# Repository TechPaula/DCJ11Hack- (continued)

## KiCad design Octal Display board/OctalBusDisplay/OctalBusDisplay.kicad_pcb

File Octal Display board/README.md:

# Octal Bus Display
This sadly never worked, and it also pulled a LOT of current (>2A), so I've abandoned it.
D

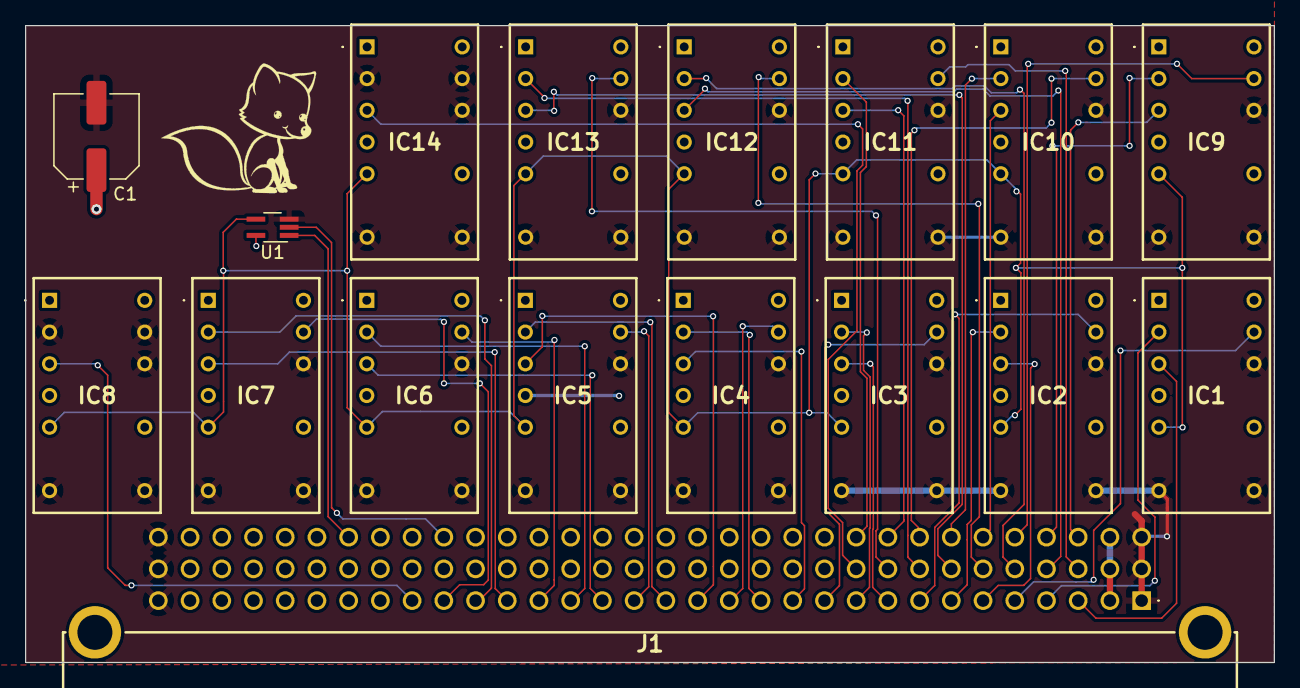
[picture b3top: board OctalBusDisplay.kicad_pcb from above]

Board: 2 copper layers, 100.0 x 51.0 mm, 18 parts (0 on the bottom side), 43 nets.

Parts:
C1: 47uF 16V; CP_Elec_6.3x5.8
IC1, IC2, IC3, IC4, IC5, IC6, IC7, IC8, IC9, IC10, IC11, IC12, IC13, IC14: TIL311
J1: 86093967113745ELF
SYM1: Logo_Open_Hardware_Large; Fox_avatar_18mm
U1: 74AHC1G08; SOT-353_SC-70-5_Handsoldering

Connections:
/DA0: IC9.3 (DATA_A), J1.C3
/DA1: IC9.2 (DATA_B), J1.C4
/DA2: IC9.13 (DATA_C), J1.C5
/DA3: IC10.3 (DATA_A), J1.C6
/DA4: IC10.2 (DATA_B), J1.C7
/DA5: IC10.13 (DATA_C), J1.C8
/DA6: IC11.3 (DATA_A), J1.C9
/DA7: IC11.2 (DATA_B), J1.C10
/DA8: IC11.13 (DATA_C), J1.B3
/DA9: IC12.3 (DATA_A), J1.B4
/DA10: IC12.2 (DATA_B), J1.B5
/DA11: IC12.13 (DATA_C), J1.B6
/DA12: IC13.3 (DATA_A), J1.B7
/DA13: IC13.2 (DATA_B), J1.B8
/DA14: IC13.13 (DATA_C), J1.B9
/DA15: IC14.3 (DATA_A), J1.B10
/LA0: IC1.3 (DATA_A), J1.A3
/LA1: IC1.2 (DATA_B), J1.A4
/LA2: IC1.13 (DATA_C), J1.A5
/LA3: IC2.3 (DATA_A), J1.A6
/LA4: IC2.2 (DATA_B), J1.A7
/LA5: IC2.13 (DATA_C), J1.A8
/LA6: IC3.3 (DATA_A), J1.A9
/LA7: IC3.2 (DATA_B), J1.A10
/LA8: IC3.13 (DATA_C), J1.A11
/LA9: IC4.3 (DATA_A), J1.A12
/LA10: IC4.2 (DATA_B), J1.A13
/LA11: IC4.13 (DATA_C), J1.A14
/LA12: IC5.3 (DATA_A), J1.A15
/LA13: IC5.2 (DATA_B), J1.A16
/LA14: IC5.13 (DATA_C), J1.A17
/LA15: IC6.3 (DATA_A), J1.A18
/LA16: IC6.2 (DATA_B), J1.A19
/LA17: IC6.13 (DATA_C), J1.A20
/LA18: IC7.3 (DATA_A), J1.A21
/LA19: IC7.2 (DATA_B), J1.A22
/LA20: IC7.13 (DATA_C), J1.A23
/LA21: IC8.3 (DATA_A), J1.A24
GND: C1.2, IC1.7 (GND), IC1.8 (BLANK), IC1.12 (DATA_D), IC2.7 (GND), IC2.8 (BLANK), IC2.12 (DATA_D), IC3.7 (GND), IC3.8 (BLANK), IC3.12 (DATA_D), IC4.7 (GND), IC4.8 (BLANK), IC4.12 (DATA_D), IC5.7 (GND), IC5.8 (BLANK), IC5.12 (DATA_D), IC6.7 (GND), IC6.8 (BLANK), IC6.12 (DATA_D), IC7.7 (GND), IC7.8 (BLANK), IC7.12 (DATA_D), IC8.2 (DATA_B), IC8.7 (GND), IC8.8 (BLANK), IC8.12 (DATA_D), IC8.13 (DATA_C), IC9.7 (GND), IC9.8 (BLANK), IC9.12 (DATA_D), IC10.7 (GND), IC10.8 (BLANK), IC10.12 (DATA_D), IC11.7 (GND), IC11.8 (BLANK), IC11.12 (DATA_D), IC12.7 (GND), IC12.8 (BLANK), IC12.12 (DATA_D), IC13.7 (GND), IC13.8 (BLANK), IC13.12 (DATA_D), IC14.2 (DATA_B), IC14.7 (GND), IC14.8 (BLANK), IC14.12 (DATA_D), IC14.13 (DATA_C), J1.A1, J1.A32, J1.B1, J1.B32, J1.C1, J1.C32, U1.3 (GND)
unnamed: IC1.5 (STROBE), IC2.5 (STROBE), IC3.5 (STROBE), IC4.5 (STROBE), IC5.5 (STROBE), IC6.5 (STROBE), IC7.5 (STROBE), IC8.5 (STROBE), IC9.5 (STROBE), IC10.5 (STROBE), IC11.5 (STROBE), IC12.5 (STROBE), IC13.5 (STROBE), IC14.5 (STROBE), U1.4
RAM_nWE: J1.C23, U1.2
VCC: C1.1, IC1.1 (LED_V), IC1.14 (VIN), IC2.1 (LED_V), IC2.14 (VIN), IC3.1 (LED_V), IC3.14 (VIN), IC4.1 (LED_V), IC4.14 (VIN), IC5.1 (LED_V), IC5.14 (VIN), IC6.1 (LED_V), IC6.14 (VIN), IC7.1 (LED_V), IC7.14 (VIN), IC8.1 (LED_V), IC8.14 (VIN), IC9.1 (LED_V), IC9.14 (VIN), IC10.1 (LED_V), IC10.14 (VIN), IC11.1 (LED_V), IC11.14 (VIN), IC12.1 (LED_V), IC12.14 (VIN), IC13.1 (LED_V), IC13.14 (VIN), IC14.1 (LED_V), IC14.14 (VIN), J1.A2, J1.B2, J1.C2, U1.5 (VCC)
nBUFCTL: J1.C26, U1.1

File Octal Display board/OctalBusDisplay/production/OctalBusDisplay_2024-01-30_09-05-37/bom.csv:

Designator,Footprint,Quantity,Value,LCSC Part #
C1,CP_Elec_6.3x5.8,1,47uF 16V,
"IC1, IC10, IC11, IC12, IC13, IC14, IC2, IC3, IC4, IC5, IC6, IC7, IC8, IC9",TIL311,14,TIL311,
J1,86093967113745ELF,1,86093967113745ELF,
U1,SOT-353_SC-70-5_Handsoldering,1,74AHC1G08,

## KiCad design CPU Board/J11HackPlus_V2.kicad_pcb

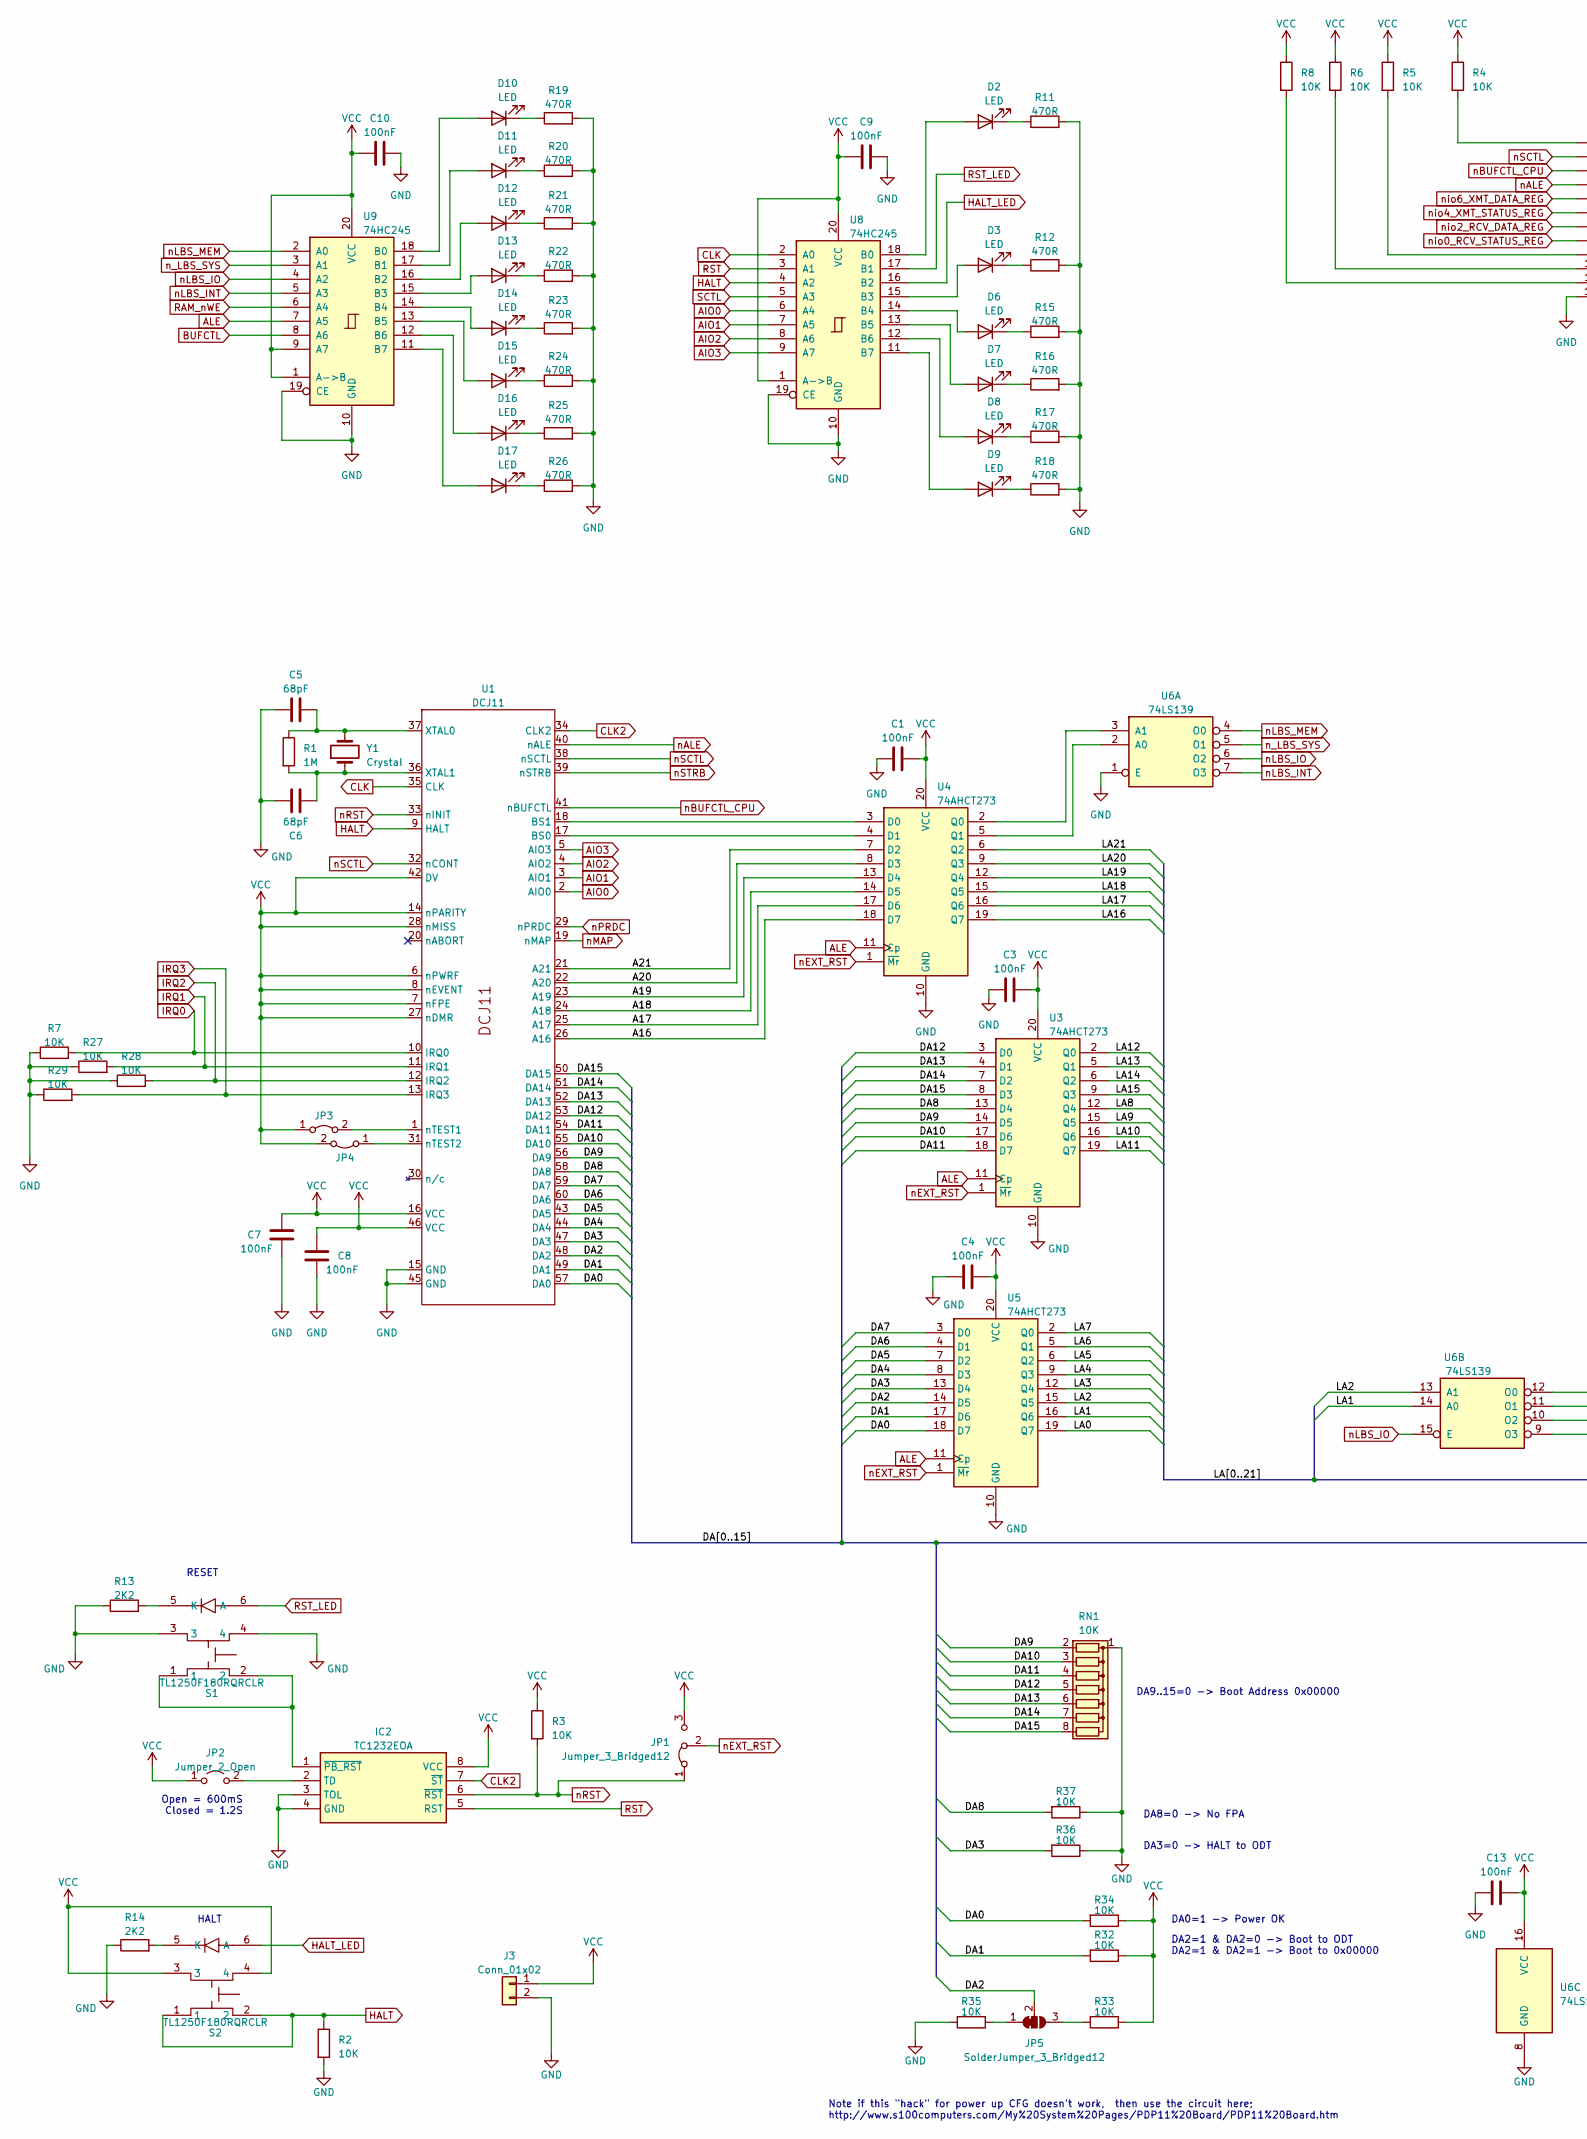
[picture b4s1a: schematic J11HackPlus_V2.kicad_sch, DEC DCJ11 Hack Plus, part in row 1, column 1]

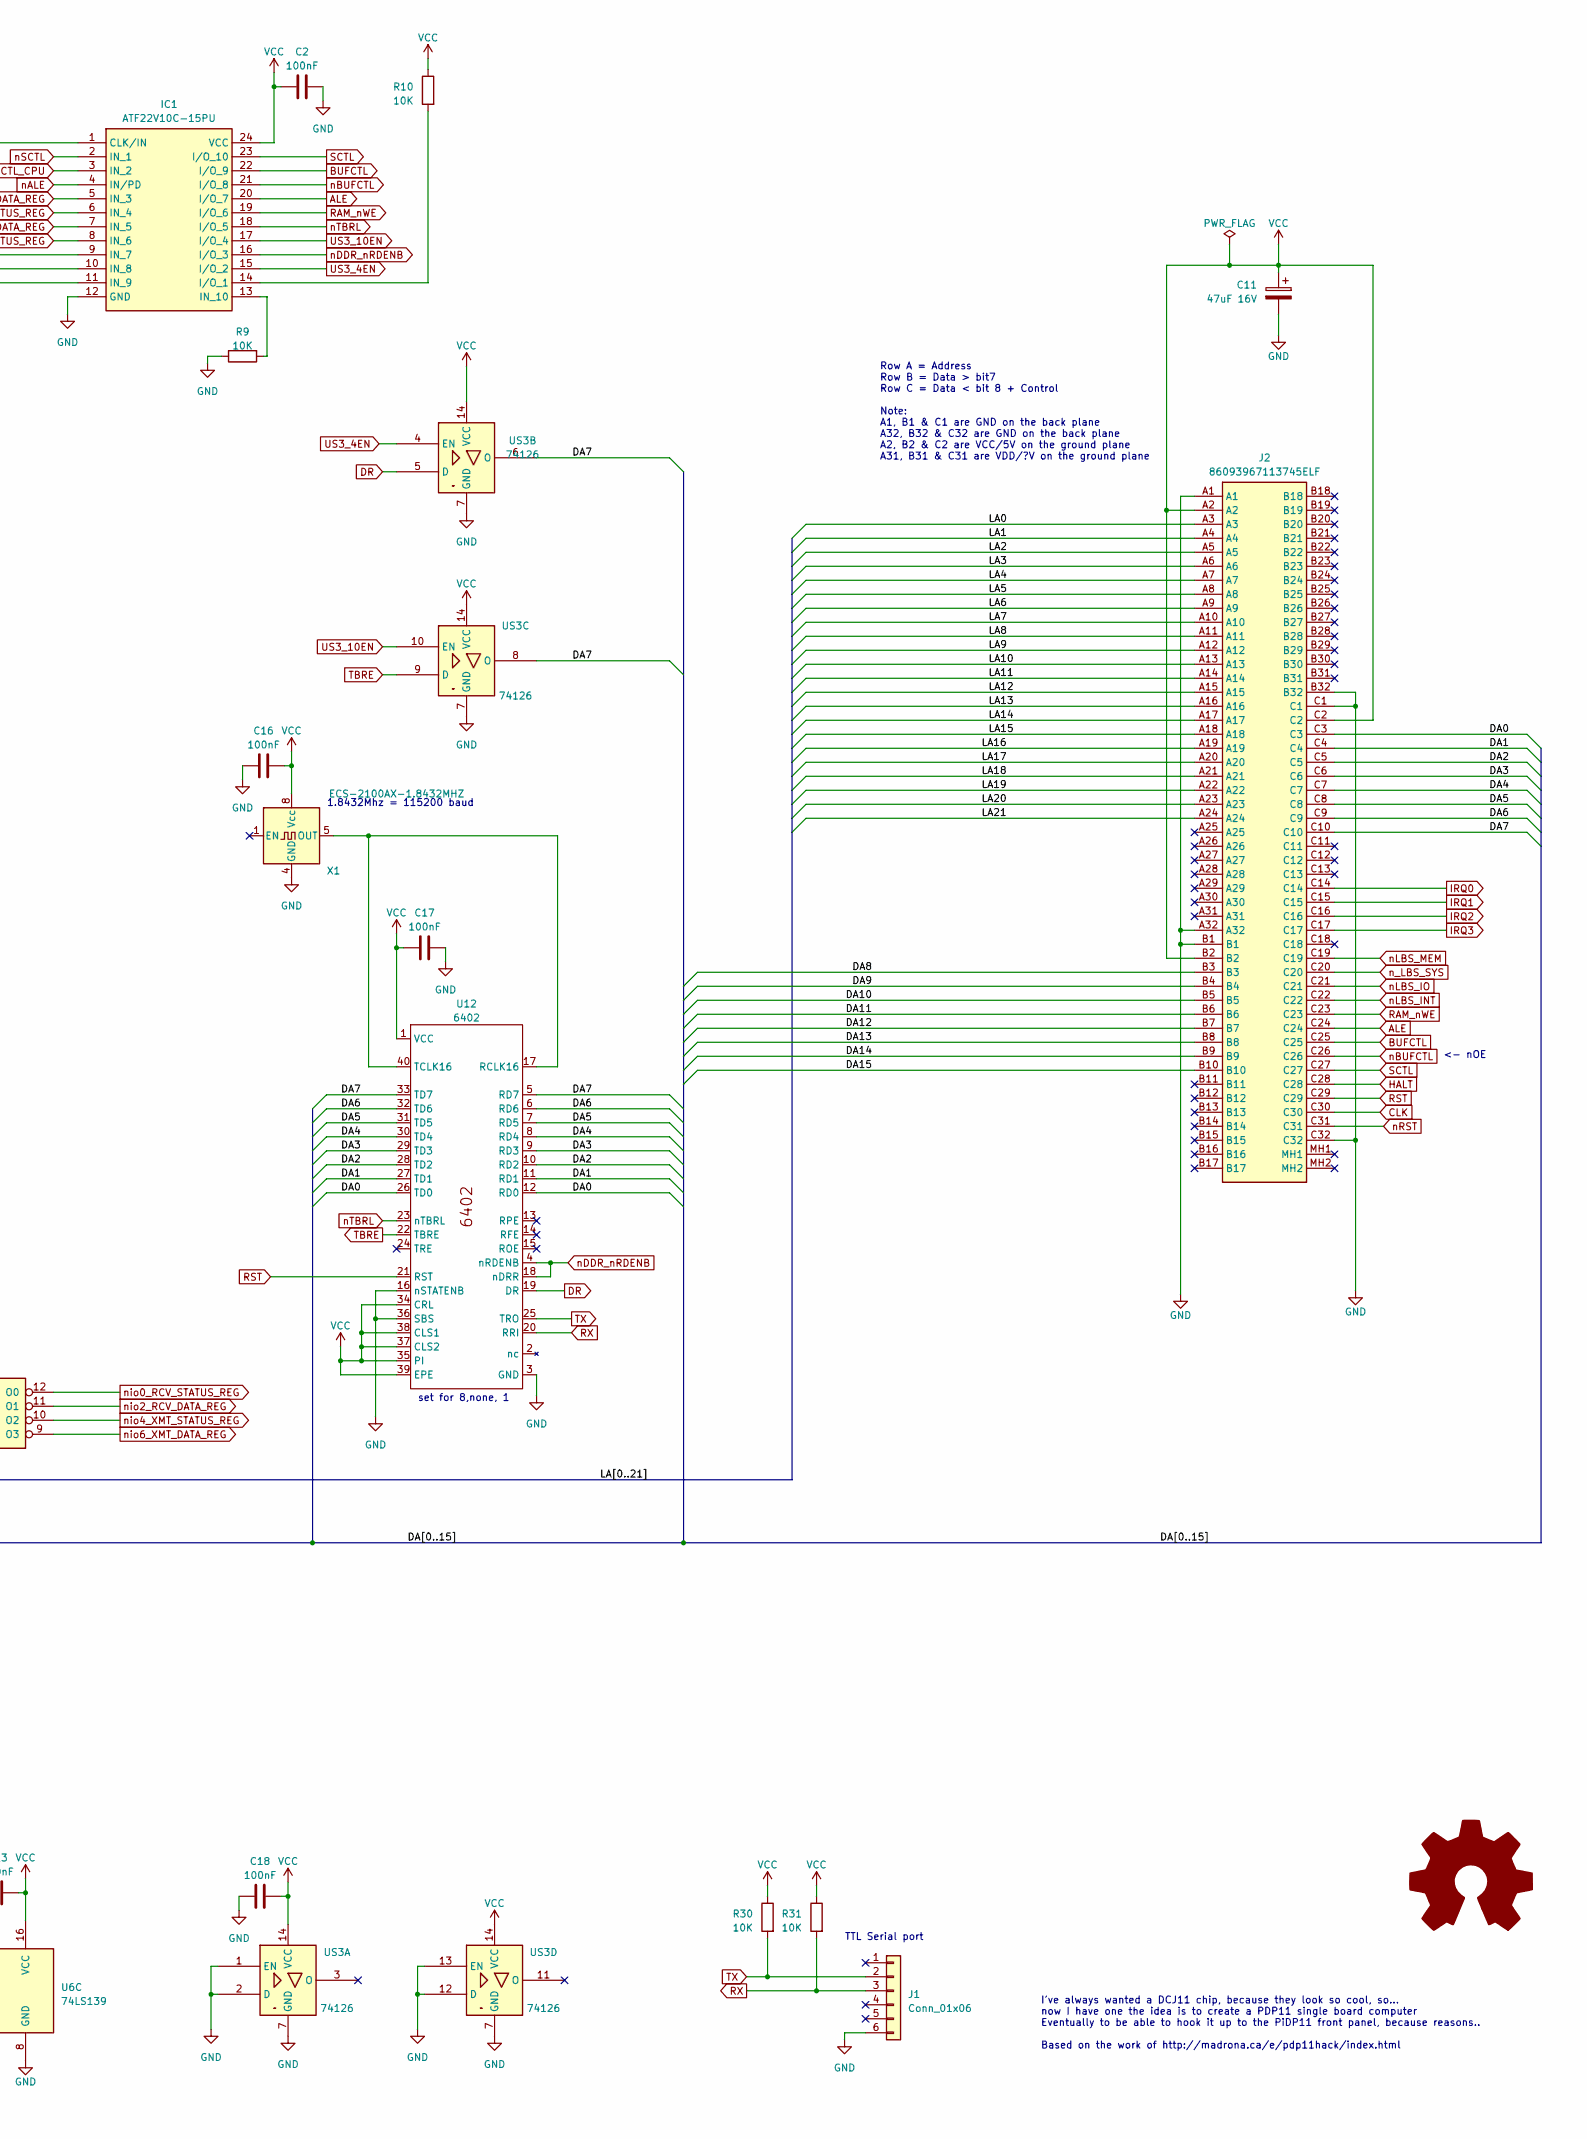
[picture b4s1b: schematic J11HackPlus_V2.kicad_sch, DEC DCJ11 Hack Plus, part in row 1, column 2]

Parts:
C1, C2, C3, C4, C7, C8, C9, C10, C13, C16, C17, C18: 100nF; C_0603_1608Metric_Pad1.08x0.95mm_HandSolder
C5, C6: 68pF; C_0603_1608Metric_Pad1.08x0.95mm_HandSolder
C11: 47uF 16V; CP_Elec_6.3x5.8
D2, D3, D6, D7, D8, D9, D10, D11, D12, D13, D14, D15, D16, D17: LED; LTL4221NHBP
IC1: ATF22V10C-15PU; DIP-24_W7.62mm; Manufacturer_Part_Number ATF22V10C-15PU; Mouser Part Number 556-AF22V10C15PU
IC2: TC1232EOA; SOIC-8_3.9x4.9mm_P1.27mm; Manufacturer_Part_Number TC1232EOA; Mouser Part Number 579-TC1232EOA
J1: Conn_01x06; PinHeader_1x06_P2.54mm_Vertical
J2: 86093967113745ELF; Manufacturer_Part_Number 86093967113745ELF
J3: Conn_01x02; Molex_KK-396_5273-02A_1x02_P3.96mm_Vertical
JP1: Jumper_3_Bridged12; SolderJumper-3_P1.3mm_Bridged2Bar12_RoundedPad1.0x1.5mm_Num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
JP2: Jumper_2_Open; SolderJumper-2_P1.3mm_Open_RoundedPad1.0x1.5mm
JP3, JP4: Jumper_2_Bridged; SolderJumper-2_P1.3mm_Bridged2Bar_RoundedPad1.0x1.5mm
JP5: SolderJumper_3_Bridged12; SolderJumper-3_P1.3mm_Bridged12_RoundedPad1.0x1.5mm_NumberL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
R1: 1M; R_0603_1608Metric_Pad0.98x0.95mm_HandSolder
R2, R3, R4, R5, R6, R7, R8, R9, R10, R27, R28, R29, R30, R31, R32, R33, R34, R35, R36, R37: 10K; R_0603_1608Metric_Pad0.98x0.95mm_HandSolder
R11, R12, R15, R16, R17, R18, R19, R20, R21, R22, R23, R24, R25, R26: 470R; R_0603_1608Metric_Pad0.98x0.95mm_HandSolder
R13, R14: 2K2; R_0603_1608Metric_Pad0.98x0.95mm_HandSolder
RN1: 10K; R_Array_SIP8
S1, S2: TL1250F180RQRCLR; Mouser Part Number 612-TL1250F180RQRCLR
SYM1: Logo_Open_Hardware_Large; Fox_avatar_18mm
U1: DCJ11; DIP-60_1300_ELL
U3, U4, U5: 74AHCT273; SSOP-20_5.3x7.2mm_P0.65mm
U6: 74LS139; SSOP-16_4.4x5.2mm_P0.65mm
U8, U9: 74HC245; TSSOP-20_4.4x6.5mm_P0.65mm
U12: 6402; DIP-40_W15.24mm_Socket
US3: 74126; SOIC-14_3.9x8.7mm_P1.27mm
X1: ECS-2100AX-1.8432MHZ; Oscillator_DIP-8
Y1: Crystal; Crystal_HC18-U_Vertical

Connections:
/A16: U1.26 (A16), U4.18 (D7)
/A17: U1.25 (A17), U4.17 (D6)
/A18: U1.24 (A18), U4.14 (D5)
/A19: U1.23 (A19), U4.13 (D4)
/A20: U1.22 (A20), U4.8 (D3)
/A21: U1.21 (A21), U4.7 (D2)
/DA0: J2.C3, R34.2, U1.57 (DA0), U5.18 (D7), U12.12 (RD0), U12.26 (TD0)
/DA1: J2.C4, R32.2, U1.49 (DA1), U5.17 (D6), U12.11 (RD1), U12.27 (TD1)
/DA2: J2.C5, JP5.2 (C), U1.48 (DA2), U5.14 (D5), U12.10 (RD2), U12.28 (TD2)
/DA3: J2.C6, R36.2, U1.47 (DA3), U5.13 (D4), U12.9 (RD3), U12.29 (TD3)
/DA4: J2.C7, U1.44 (DA4), U5.8 (D3), U12.8 (RD4), U12.30 (TD4)
/DA5: J2.C8, U1.43 (DA5), U5.7 (D2), U12.7 (RD5), U12.31 (TD5)
/DA6: J2.C9, U1.60 (DA6), U5.4 (D1), U12.6 (RD6), U12.32 (TD6)
/DA7: J2.C10, U1.59 (DA7), U5.3 (D0), U12.5 (RD7), U12.33 (TD7), US3.6 (O), US3.8 (O)
/DA8: J2.B3, R37.2, U1.58 (DA8), U3.13 (D4)
/DA9: J2.B4, RN1.2 (R1), U1.56 (DA9), U3.14 (D5)
/DA10: J2.B5, RN1.3 (R2), U1.55 (DA10), U3.17 (D6)
/DA11: J2.B6, RN1.4 (R3), U1.54 (DA11), U3.18 (D7)
/DA12: J2.B7, RN1.5 (R4), U1.53 (DA12), U3.3 (D0)
/DA13: J2.B8, RN1.6 (R5), U1.52 (DA13), U3.4 (D1)
/DA14: J2.B9, RN1.7 (R6), U1.51 (DA14), U3.7 (D2)
/DA15: J2.B10, RN1.8 (R7), U1.50 (DA15), U3.8 (D3)
/LA0: J2.A3, U5.19 (Q7)
/LA1: J2.A4, U5.16 (Q6), U6.14 (A0)
/LA2: J2.A5, U5.15 (Q5), U6.13 (A1)
/LA3: J2.A6, U5.12 (Q4)
/LA4: J2.A7, U5.9 (Q3)
/LA5: J2.A8, U5.6 (Q2)
/LA6: J2.A9, U5.5 (Q1)
/LA7: J2.A10, U5.2 (Q0)
/LA8: J2.A11, U3.12 (Q4)
/LA9: J2.A12, U3.15 (Q5)
/LA10: J2.A13, U3.16 (Q6)
/LA11: J2.A14, U3.19 (Q7)
/LA12: J2.A15, U3.2 (Q0)
/LA13: J2.A16, U3.5 (Q1)
/LA14: J2.A17, U3.6 (Q2)
/LA15: J2.A18, U3.9 (Q3)
/LA16: J2.A19, U4.19 (Q7)
/LA17: J2.A20, U4.16 (Q6)
/LA18: J2.A21, U4.15 (Q5)
/LA19: J2.A22, U4.12 (Q4)
/LA20: J2.A23, U4.9 (Q3)
/LA21: J2.A24, U4.6 (Q2)
AIO0: U1.2 (AIO0), U8.6 (A4)
AIO1: U1.3 (AIO1), U8.7 (A5)
AIO2: U1.4 (AIO2), U8.8 (A6)
AIO3: U1.5 (AIO3), U8.9 (A7)
ALE: IC1.20 (I/O_7), J2.C24, U3.11 (Cp), U4.11 (Cp), U5.11 (Cp), U9.7 (A5)
BUFCTL: IC1.22 (I/O_9), J2.C25, U9.8 (A6)
CLK: J2.C30, U1.35 (CLK), U8.2 (A0)
CLK2: IC2.7 (~ST), U1.34 (CLK2)
DR: U12.19 (DR), US3.5 (D)
GND: C1.1, C2.1, C3.1, C4.1, C5.1, C6.2, C7.1, C8.1, C9.1, C10.1, C11.2, C13.1, C16.1, C17.1, C18.1, IC1.12 (GND), IC2.3 (TOL), IC2.4 (GND), J1.6, J2.A1, J2.A32, J2.B1, J2.B32, J2.C1, J2.C32, J3.2, R2.2, R7.1, R9.1, R11.2, R12.2, R13.1, R14.1, R15.2, R16.2, R17.2, R18.2, R19.2, R20.2, R21.2, R22.2, R23.2, R24.2, R25.2, R26.2, R27.1, R28.1, R29.1, R35.2, R36.1, R37.1, RN1.1 (common), S1.3, S1.4, U1.15 (GND), U1.45 (GND), U3.10 (GND), U4.10 (GND), U5.10 (GND), U6.1 (E), U6.8 (GND), U8.10 (GND), U8.19 (CE), U9.10 (GND), U9.19 (CE), U12.3 (GND), U12.16 (nSTATENB), U12.36 (SBS), US3.1 (EN), US3.2 (D), US3.7 (GND), US3.12 (D), US3.13 (EN), X1.4 (GND)
HALT: J2.C28, R2.1, S2.1, S2.2, U1.9 (HALT), U8.4 (A2)
HALT_LED: S2.6 (A), U8.16 (B2)
IRQ0: J2.C14, R7.2, U1.10 (IRQ0)
IRQ1: J2.C15, R27.2, U1.11 (IRQ1)
IRQ2: J2.C16, R28.2, U1.12 (IRQ2)
IRQ3: J2.C17, R29.2, U1.13 (IRQ3)
unnamed: D2.2 (A), U8.18 (B0)
unnamed: D2.1 (K), R11.1
unnamed: D3.2 (A), U8.15 (B3)
unnamed: D3.1 (K), R12.1
unnamed: D6.2 (A), U8.14 (B4)
unnamed: D6.1 (K), R15.1
unnamed: D7.2 (A), U8.13 (B5)
unnamed: D7.1 (K), R16.1
unnamed: D8.2 (A), U8.12 (B6)
unnamed: D8.1 (K), R17.1
unnamed: D9.2 (A), U8.11 (B7)
unnamed: D9.1 (K), R18.1
unnamed: D10.2 (A), U9.18 (B0)
unnamed: D10.1 (K), R19.1
unnamed: D11.2 (A), U9.17 (B1)
unnamed: D11.1 (K), R20.1
unnamed: D12.2 (A), U9.16 (B2)
unnamed: D12.1 (K), R21.1
unnamed: D13.2 (A), U9.15 (B3)
unnamed: D13.1 (K), R22.1
unnamed: D14.2 (A), U9.14 (B4)
unnamed: D14.1 (K), R23.1
unnamed: D15.2 (A), U9.13 (B5)
unnamed: D15.1 (K), R24.1
unnamed: D16.2 (A), U9.12 (B6)
unnamed: D16.1 (K), R25.1
unnamed: D17.2 (A), U9.11 (B7)
unnamed: D17.1 (K), R26.1
unnamed: IC1.1 (CLK/IN), R4.2
unnamed: IC1.9 (IN_7), R5.2
unnamed: IC1.10 (IN_8), R6.2
unnamed: IC1.11 (IN_9), R8.2
unnamed: IC1.13 (IN_10), R9.2
unnamed: IC1.14 (I/O_1), R10.2
unnamed: IC2.2 (TD), JP2.2 (B)
unnamed: IC2.1 (~PB_RST), S1.1, S1.2
unnamed: JP3.2 (B), U1.1 (nTEST1)
unnamed: JP4.1 (A), U1.31 (nTEST2)
unnamed: JP5.1 (A), R35.1
unnamed: JP5.3 (B), R33.2
unnamed: R13.2, S1.5 (K)
unnamed: R14.2, S2.5 (K)
unnamed: U1.17 (BS0), U4.4 (D1)
unnamed: U1.18 (BS1), U4.3 (D0)
unnamed: C5.2, R1.1, U1.37 (XTAL0), Y1.2
unnamed: C6.1, R1.2, U1.36 (XTAL1), Y1.1
unnamed: U4.2 (Q0), U6.3 (A1)
unnamed: U4.5 (Q1), U6.2 (A0)
unnamed: U12.17 (RCLK16), U12.40 (TCLK16), X1.5 (OUT)
RAM_nWE: IC1.19 (I/O_6), J2.C23, U9.6 (A4)
RST: IC2.5 (RST), J2.C29, U8.3 (A1), U12.21 (RST)
RST_LED: S1.6 (A), U8.17 (B1)
RX: J1.3, R31.2, U12.20 (RRI)
SCTL: IC1.23 (I/O_10), J2.C27, U8.5 (A3)
TBRE: U12.22 (TBRE), US3.9 (D)
TX: J1.2, R30.2, U12.25 (TRO)
US3_4EN: IC1.15 (I/O_2), US3.4 (EN)
US3_10EN: IC1.17 (I/O_4), US3.10 (EN)
VCC: C1.2, C2.2, C3.2, C4.2, C7.2, C8.2, C9.2, C10.2, C11.1, C13.2, C16.2, C17.2, C18.2, IC1.24 (VCC), IC2.8 (VCC), J2.A2, J2.B2, J2.C2, J3.1, JP1.3 (B), JP2.1 (A), JP3.1 (A), JP4.2 (B), R3.1, R4.1, R5.1, R6.1, R8.1, R10.1, R30.1, R31.1, R32.1, R33.1, R34.1, S2.3, S2.4, U1.6 (nPWRF), U1.7 (nFPE), U1.8 (nEVENT), U1.14 (nPARITY), U1.16 (VCC), U1.27 (nDMR), U1.28 (nMISS), U1.42 (DV), U1.46 (VCC), U3.20 (VCC), U4.20 (VCC), U5.20 (VCC), U6.16 (VCC), U8.1 (A->B), U8.20 (VCC), U9.1 (A->B), U9.9 (A7), U9.20 (VCC), U12.1 (VCC), U12.34 (CRL), U12.35 (PI), U12.37 (CLS2), U12.38 (CLS1), U12.39 (EPE), US3.14 (VCC), X1.8 (Vcc)
nALE: IC1.4 (IN/PD), U1.40 (nALE)
nBUFCTL: IC1.21 (I/O_8), J2.C26
nBUFCTL_CPU: IC1.3 (IN_2), U1.41 (nBUFCTL)
nDDR_nRDENB: IC1.16 (I/O_3), U12.4 (nRDENB), U12.18 (nDRR)
nEXT_RST: JP1.2 (C), U3.1 (~Mr), U4.1 (~Mr), U5.1 (~Mr)
nLBS_INT: J2.C22, U6.7 (O3), U9.5 (A3)
nLBS_IO: J2.C21, U6.6 (O2), U6.15 (E), U9.4 (A2)
nLBS_MEM: J2.C19, U6.4 (O0), U9.2 (A0)
nMAP: U1.19 (nMAP)
nPRDC: U1.29 (nPRDC)
nRST: IC2.6 (~RST), J2.C31, JP1.1 (A), R3.2, U1.33 (nINIT)
nSCTL: IC1.2 (IN_1), U1.32 (nCONT), U1.38 (nSCTL)
nSTRB: U1.39 (nSTRB)
nTBRL: IC1.18 (I/O_5), U12.23 (nTBRL)
n_LBS_SYS: J2.C20, U6.5 (O1), U9.3 (A1)
nio0_RCV_STATUS_REG: IC1.8 (IN_6), U6.12 (O0)
nio2_RCV_DATA_REG: IC1.7 (IN_5), U6.11 (O1)
nio4_XMT_STATUS_REG: IC1.6 (IN_4), U6.10 (O2)
nio6_XMT_DATA_REG: IC1.5 (IN_3), U6.9 (O3)

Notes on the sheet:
Row A = Address Row B = Data > bit7 Row C = Data < bit 8 + Control Note: A1, B1 & C1 are GND on the back plane A32, B32 & C32 are GND on the back plane A2, B2 & C2 are VCC/5V on the ground plane A31, B31 & C31 are VDD/?V on the ground plane
DA0=1 -> Power OK
DA8=0 -> No FPA
<- nOE
Open = 600mS Closed = 1.2S
DA2=1 & DA2=0 -> Boot to ODT DA2=1 & DA2=1 -> Boot to 0x00000
HALT
I've always wanted a DCJ11 chip, because they look so cool, so... now I have one the idea is to create a PDP11 single board computer Eventually to be able to hook it up to the PiDP11 front panel, because reasons.. Based on the work of http://madrona.ca/e/pdp11hack/index.html
1.8432Mhz = 115200 baud
set for 8,none, 1
RESET
DA3=0 -> HALT to ODT
Note if this "hack" for power up CFG doesn't work, then use the circuit here; http://www.s100computers.com/My%20System%20Pages/PDP11%20Board/PDP11%20Board.htm
DA9..15=0 -> Boot Address 0x00000
TTL Serial port

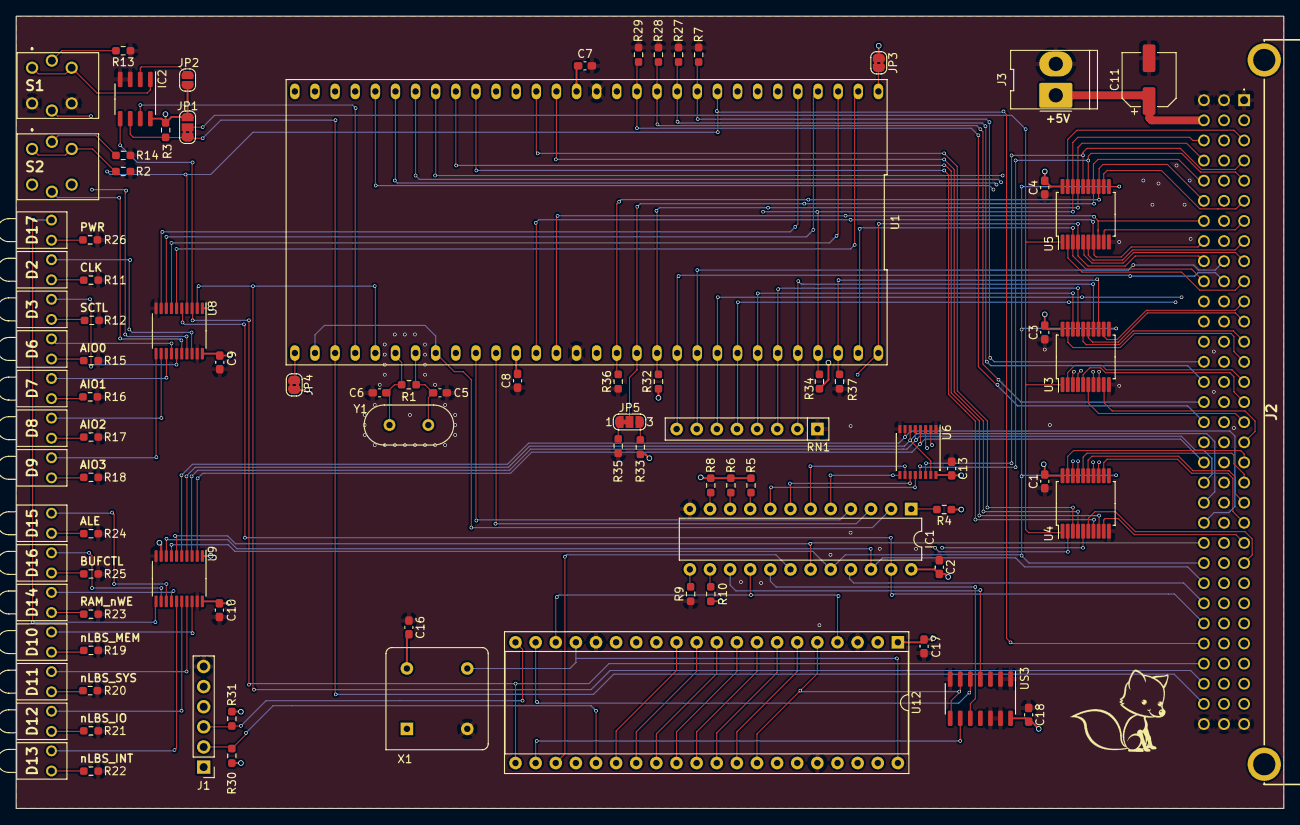
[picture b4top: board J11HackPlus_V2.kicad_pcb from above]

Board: 4 copper layers, 160.0 x 100.0 mm, 91 parts (0 on the bottom side), 135 nets.

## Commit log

2024-01-07 Added Files
    Added all files from the project along with example code.
2024-01-07 Updated readme
    Added link to image
2024-01-07 Updated readme
    Added link to backplane supplier
2024-01-07 Update mistakes in .oct files
    Updated a couple of .oct files with missing rs/340 lines
2024-01-26 Added "Hellorld!"
2024-01-26 Added better picture of CPU card and Hellorld!
2024-02-04 Octal Bus Display (WIP)
    Added PCB for Octal Bus Display
2024-02-04 Auto stash before merge of "main" and "origin/main"
2024-04-07 Adjust memory map
    Moved the memory map around so that I can add the dotmatrix display I want to add. These are now;
    HEX
    0x0000 - 0x7FFF = RAM (32K)
    0x6000 - 0x7FFF = Text Display (shadowed in RAM as it's WRITE only)
    0x8000 - 0xBFFF = ROM (16K)
    0xC000 - 0xDFFF = Future (Matrix display)
2024-08-13 Added 16x16 dotmatrix display PCB and test code
2024-08-13 Update README
    Updated readme and added 16x16 images,
2024-08-13 Fixed list in readme
2024-08-13 further update to readme.
2024-08-13 final tweaks to readme (I hope)
2024-08-25 Update with correct chips (no change to PCB)
2024-11-23 working on GoL assembly code,
2024-11-23 added ".org" to emulator code
    added ".org" to emulator code and updated code to use labels and .org
2024-11-24 fixed a number of bugs and removed the use of r6 in places for JSR
2024-11-24 I missed one jsr
